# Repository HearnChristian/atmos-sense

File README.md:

# atmos-sense
Summer 2026 project to build familiarity with atmospheric sensor systems, drone integration, and all necessary concepts.

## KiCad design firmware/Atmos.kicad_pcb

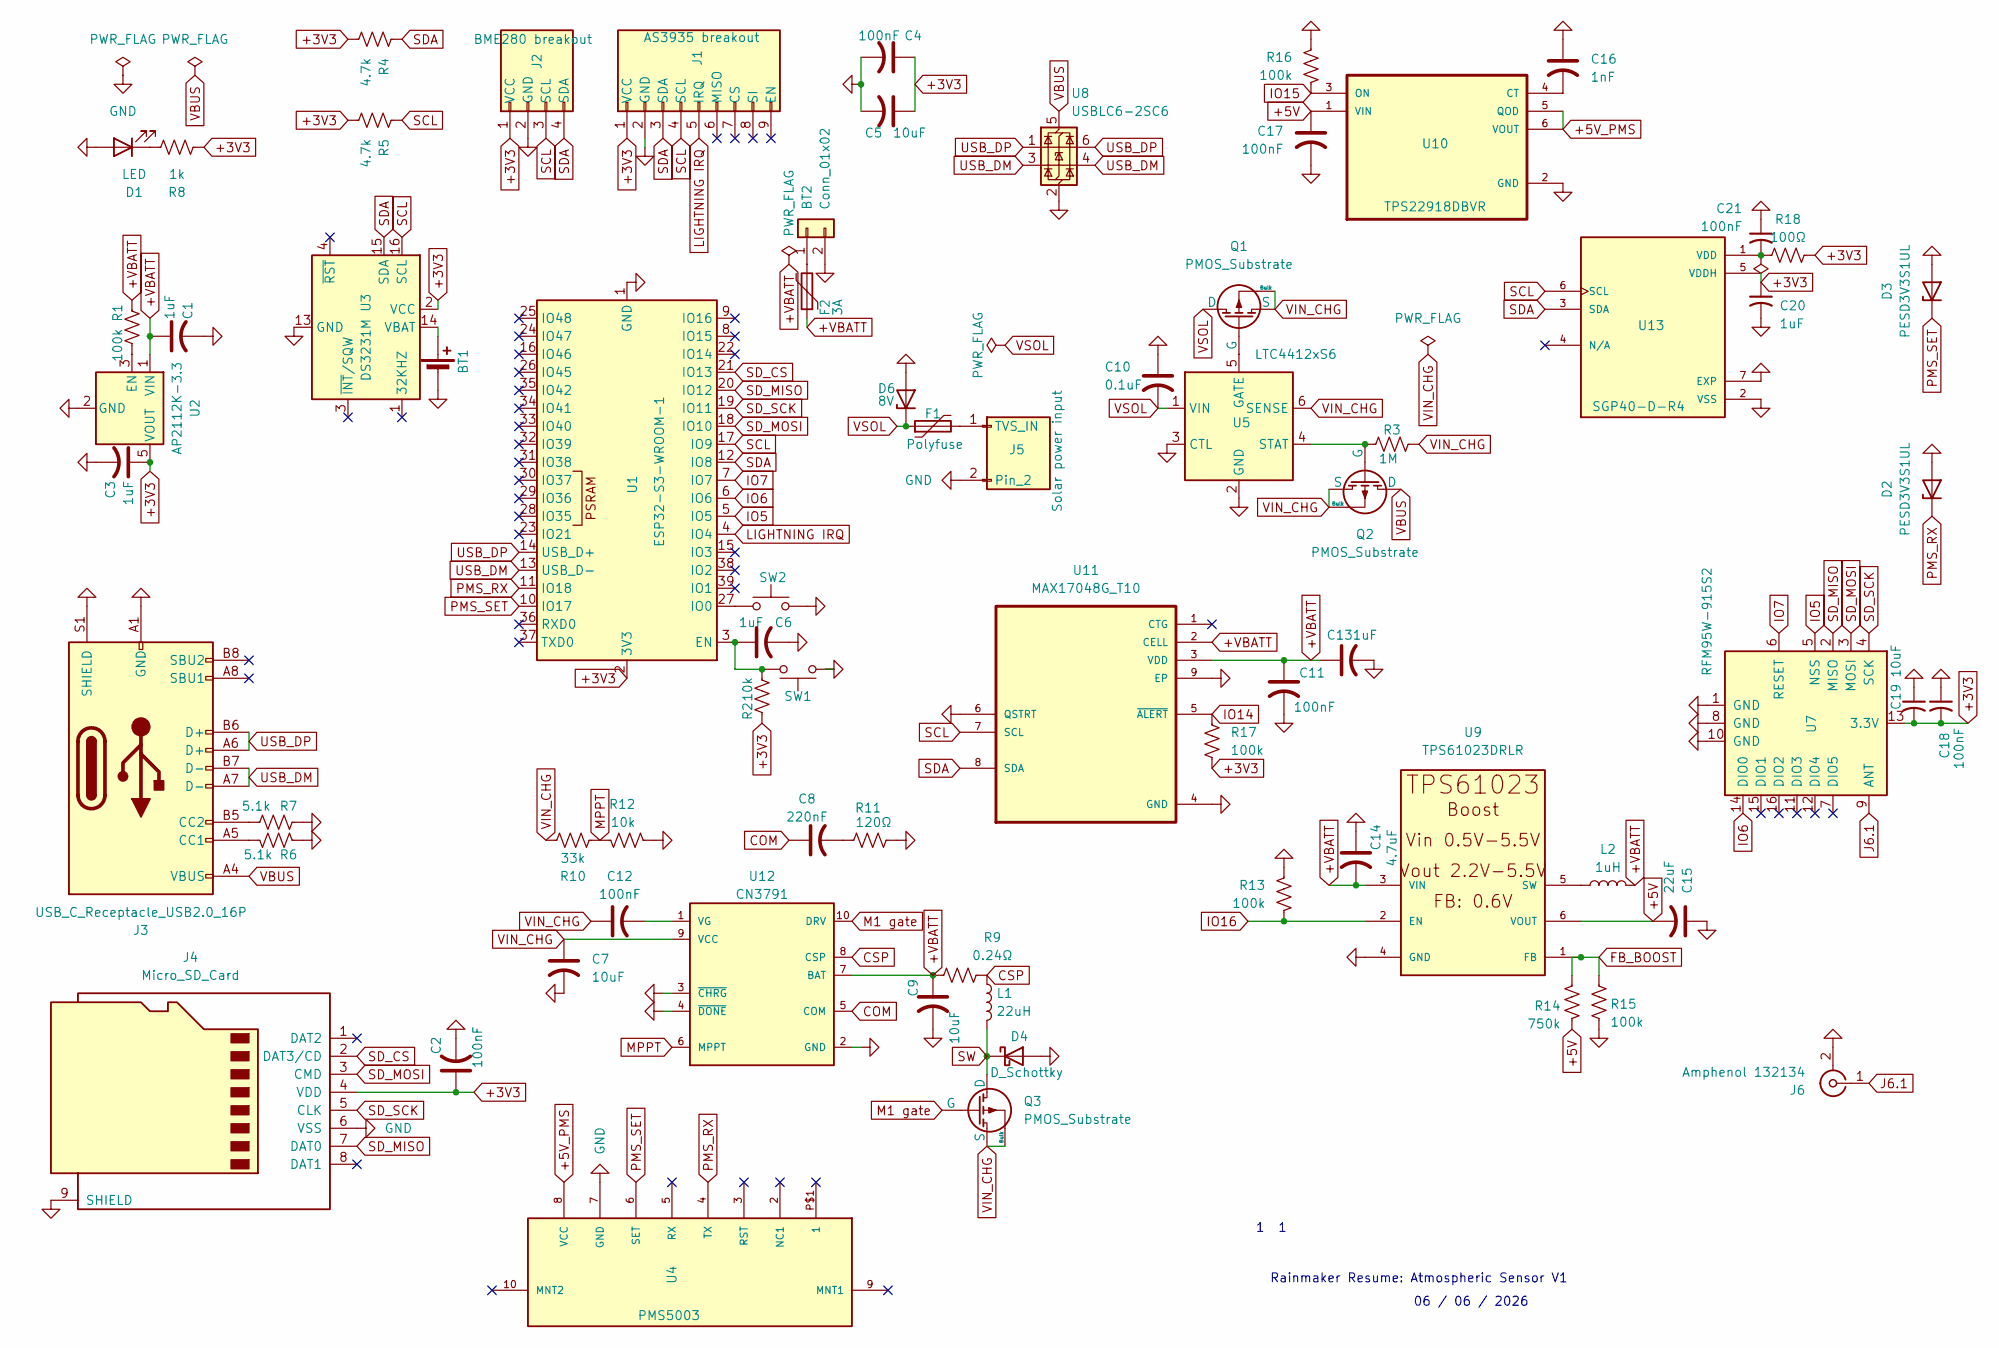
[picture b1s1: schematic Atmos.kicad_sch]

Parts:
BT1: Battery_Cell; BatteryHolder_Keystone_3034_1x20mm
BT2: Conn_01x02; JST_PH_S2B-PH-K_1x02_P2.00mm_Horizontal
C1, C3, C6, C13, C20: 1uF; C_0603_1608Metric
C2, C4, C11, C12, C17, C18, C21: 100nF; C_0603_1608Metric
C5, C7, C9, C19: 10uF; C_0805_2012Metric
C8: 220nF; C_0603_1608Metric
C10: 0.1uF; C_0603_1608Metric
C14: 4.7uF; C_0603_1608Metric
C15: 22uF; C_0805_2012Metric
C16: 1nF; C_0603_1608Metric
D1: LED; LED_0805_2012Metric
D2, D3: PESD3V3S1UL; D_SOD-882
D4: D_Schottky; D_SMA
D6: 8V; D_SOD-123
F1: Polyfuse; Fuse_1812_4532Metric
F2: 3A; Fuse_1812_4532Metric
J1: AS3935 breakout; PinSocket_1x09_P2.54mm_Vertical
J2: BME280 breakout; PinSocket_1x04_P2.54mm_Vertical
J3: USB_C_Receptacle_USB2.0_16P; USB_C_Receptacle_HRO_TYPE-C-31-M-12
J4: Micro_SD_Card; microSD_HC_Hirose_DM3AT-SF-PEJM5
J5: Solar power input; JST_XH_B2B-XH-A_1x02_P2.50mm_Vertical
J6: Amphenol 132134; SMA_Amphenol_132134_Vertical
L1: 22uH; L_Bourns_SRN6045TA
L2: 1uH; L_Coilcraft_1008HQ_2520Metric
Q1, Q2, Q3: PMOS_Substrate; SOT-23
R1, R13, R15, R16, R17: 100k; R_0603_1608Metric
R2, R12: 10k; R_0603_1608Metric
R3: 1M; R_0603_1608Metric
R4, R5: 4.7k; R_0603_1608Metric
R6, R7: 5.1k; R_0603_1608Metric
R8: 1k; R_0603_1608Metric
R9: 0.24Ω; R_1206_3216Metric
R10: 33k; R_0603_1608Metric
R11: 120Ω; R_0603_1608Metric
R14: 750k; R_0603_1608Metric
R18: 100Ω; R_0603_1608Metric
SW1: SW_Push_1P1T_NO_CK_KMR2
SW2: SW_Push; SW_Push_1P1T_NO_CK_KMR2
U1: ESP32-S3-WROOM-1
U2: AP2112K-3.3; SOT-23-5
U3: DS3231M; SOIC-16W_7.5x10.3mm_P1.27mm
U4: PMS5003; Molex_PicoBlade_53398-0871_1x08-1MP_P1.25mm_Vertical
U5: LTC4412xS6; TSOT-23-6
U7: RFM95W-915S2; HOPERF_RFM9XW_SMD
U8: USBLC6-2SC6; SOT-23-6
U9: TPS61023DRLR; SOT-563
U10: TPS22918DBVR; SOT-23-6
U11: MAX17048G_T10; DFN-8-1EP_2x2mm_P0.5mm_EP0.9x1.5mm
U12: CN3791; MSOP-10_3x3mm_P0.5mm
U13: SGP40-D-R4; DFN-6-1EP_2x2mm_P0.5mm_EP0.7x1.6mm; PARTREV 1.2

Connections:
+3V3: C2.1, C3.1, C4.1, C5.1, C18.2, C19.2, C20.1, J1.1 (VCC), J2.1 (VCC), J4.4 (VDD), R2.2, R4.2, R5.2, R8.1, R17.2, R18.2, U1.2 (3V3), U2.5 (VOUT), U3.2 (VCC), U7.13 (3.3V), U13.5 (VDDH)
+5V: C15.2, C17.1, R14.2, U9.6 (VOUT), U10.1 (VIN)
+5V_PMS: U4.8 (VCC), U10.5 (QOD), U10.6 (VOUT)
+VBATT: C1.1, C9.1, C11.1, C13.1, C14.2, F2.1, L2.2, R1.1, R9.1, U2.1 (VIN), U9.3 (VIN), U11.2 (CELL), U11.3 (VDD), U12.7 (BAT)
COM: C8.1, U12.5 (COM)
CSP: L1.1, R9.2, U12.8 (CSP)
FB_BOOST: R14.1, R15.1, U9.1 (FB)
GND: BT1.2 (-), BT2.2, C1.2, C2.2, C3.2, C4.2, C5.2, C6.2, C7.2, C9.2, C10.1, C11.2, C13.2, C14.1, C15.1, C16.1, C17.2, C18.1, C19.1, C20.2, C21.1, D1.2 (A), D2.2 (A), D3.2 (A), D4.2 (A), D6.2 (A), J1.2 (GND), J2.2 (GND), J3.A1 (GND), J3.A12 (GND), J3.B1 (GND), J3.B12 (GND), J3.S1 (SHIELD), J4.6 (VSS), J4.9 (SHIELD), J5.2, J6.2 (Ext), R6.2, R7.2, R11.2, R12.2, R13.1, R15.2, R16.1, SW1.1, SW2.2, U1.1 (GND), U1.40 (GND), U1.41 (GND), U2.2 (GND), U3.5 (GND), U3.6 (GND), U3.7 (GND), U3.8 (GND), U3.9 (GND), U3.10 (GND), U3.11 (GND), U3.12 (GND), U3.13 (GND), U4.7 (GND), U5.2 (GND), U5.3 (CTL), U7.1 (GND), U7.8 (GND), U7.10 (GND), U8.2 (GND), U9.4 (GND), U10.2 (GND), U11.4 (GND), U11.6 (QSTRT), U11.9 (EP), U12.2 (GND), U12.3 (~CHRG), U12.4 (~DONE), U13.2 (VSS), U13.7 (EXP)
IO5: U1.5 (IO5), U7.5 (NSS)
IO6: U1.6 (IO6), U7.14 (DIO0)
IO7: U1.7 (IO7), U7.6 (RESET)
IO14: R17.1, U11.5 (~ALERT)
IO15: R16.2, U10.3 (ON)
IO16: R13.2, U9.2 (EN)
J6.1: J6.1 (In), U7.9 (ANT)
LIGHTNING IRQ: J1.5 (IRQ), U1.4 (IO4)
M1 gate: Q3.2 (G), U12.10 (DRV)
MPPT: R10.1, R12.1, U12.6 (MPPT)
unnamed: BT1.1 (+), U3.14 (VBAT)
unnamed: BT2.1, F2.2
unnamed: C8.2, R11.1
unnamed: D1.1 (K), R8.2
unnamed: J3.A5 (CC1), R6.1
unnamed: J3.B5 (CC2), R7.1
unnamed: F1.2, J5.1 (TVS_IN)
unnamed: Q1.2 (G), U5.5 (GATE)
unnamed: Q2.2 (G), R3.1, U5.4 (STAT)
unnamed: C6.1, R2.1, SW1.2, U1.3 (EN)
unnamed: SW2.1, U1.27 (IO0)
unnamed: R1.2, U2.3 (EN)
unnamed: L2.1, U9.5 (SW)
unnamed: C16.2, U10.4 (CT)
unnamed: C12.2, U12.1 (VG)
unnamed: C21.2, R18.1, U13.1 (VDD)
PMS_RX: D2.1 (K), U1.11 (IO18), U4.4 (TX)
PMS_SET: D3.1 (K), U1.10 (IO17), U4.6 (SET)
SCL: J1.4 (SCL), J2.3 (SCL), R5.1, U1.17 (IO9), U3.16 (SCL), U11.7 (SCL), U13.6 (SCL)
SDA: J1.3 (SDA), J2.4 (SDA), R4.1, U1.12 (IO8), U3.15 (SDA), U11.8 (SDA), U13.3 (SDA)
SD_CS: J4.2 (DAT3/CD), U1.21 (IO13)
SD_MISO: J4.7 (DAT0), U1.20 (IO12), U7.2 (MISO)
SD_MOSI: J4.3 (CMD), U1.18 (IO10), U7.3 (MOSI)
SD_SCK: J4.5 (CLK), U1.19 (IO11), U7.4 (SCK)
SW: D4.1 (K), L1.2, Q3.1 (D)
USB_DM: J3.A7 (D-), J3.B7 (D-), U1.13 (USB_D-), U8.3 (I/O2), U8.4 (I/O2)
USB_DP: J3.A6 (D+), J3.B6 (D+), U1.14 (USB_D+), U8.1 (I/O1), U8.6 (I/O1)
VBUS: J3.A4 (VBUS), J3.A9 (VBUS), J3.B4 (VBUS), J3.B9 (VBUS), Q2.1 (D), U8.5 (VBUS)
VIN_CHG: C7.1, C12.1, Q1.3 (S), Q1.4 (Bulk), Q2.3 (S), Q2.4 (Bulk), Q3.3 (S), Q3.4 (Bulk), R3.2, R10.2, U5.6 (SENSE), U12.9 (VCC)
VSOL: C10.2, D6.1 (K), F1.1, Q1.1 (D), U5.1 (VIN)

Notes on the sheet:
06 / 06 / 2026
1 1
Rainmaker Resume: Atmospheric Sensor V1

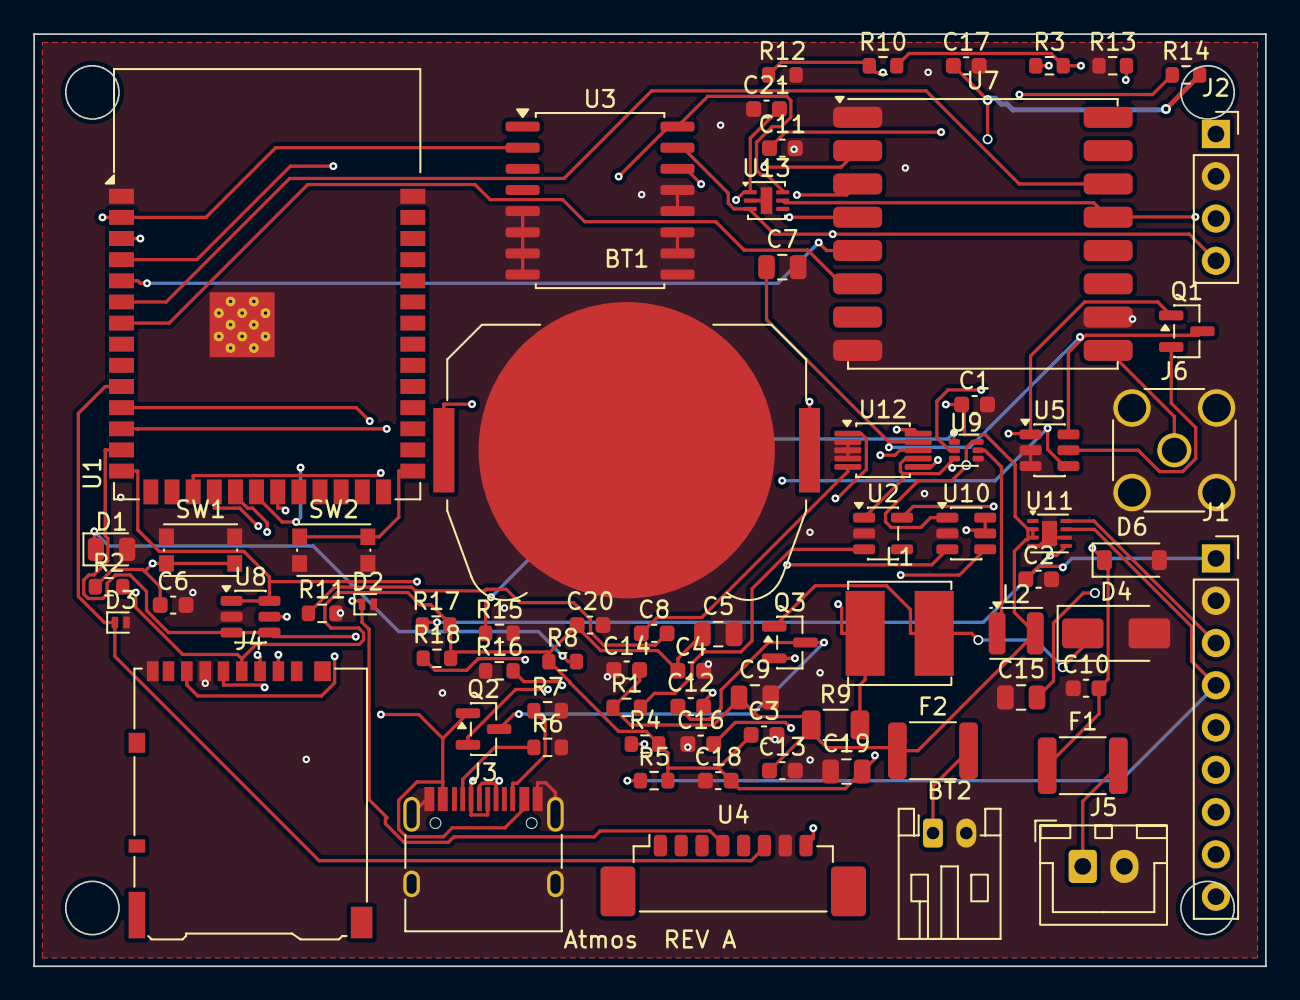
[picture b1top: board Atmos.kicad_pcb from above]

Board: 4 copper layers, 74.0 x 56.0 mm, 73 parts (0 on the bottom side), 48 nets.

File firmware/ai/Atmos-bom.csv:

"Refs","Value","Footprint","Qty","DNP"
"BT1","Battery_Cell","Battery:BatteryHolder_Keystone_3034_1x20mm","1",""
"BT2","Conn_01x02","Connector_JST:JST_PH_S2B-PH-K_1x02_P2.00mm_Horizontal","1",""
"C1","1uF","Capacitor_SMD:C_0603_1608Metric","1",""
"C2","100nF","Capacitor_SMD:C_0603_1608Metric","1",""
"C3","1uF","Capacitor_SMD:C_0603_1608Metric","1",""
"C4","100nF","Capacitor_SMD:C_0603_1608Metric","1",""
"C5","10uF","Capacitor_SMD:C_0805_2012Metric","1",""
"C6","1uF","Capacitor_SMD:C_0603_1608Metric","1",""
"C7","10uF","Capacitor_SMD:C_0805_2012Metric","1",""
"C8","220nF","Capacitor_SMD:C_0603_1608Metric","1",""
"C9","10uF","Capacitor_SMD:C_0805_2012Metric","1",""
"C10","0.1uF","Capacitor_SMD:C_0603_1608Metric","1",""
"C11","100nF","Capacitor_SMD:C_0603_1608Metric","1",""
"C12","100nF","Capacitor_SMD:C_0603_1608Metric","1",""
"C13","1uF","Capacitor_SMD:C_0603_1608Metric","1",""
"C14","4.7uF","Capacitor_SMD:C_0603_1608Metric","1",""
"C15","22uF","Capacitor_SMD:C_0805_2012Metric","1",""
"C16","1nF","Capacitor_SMD:C_0603_1608Metric","1",""
"C17","100nF","Capacitor_SMD:C_0603_1608Metric","1",""
"C18","100nF","Capacitor_SMD:C_0603_1608Metric","1",""
"C19","10uF","Capacitor_SMD:C_0805_2012Metric","1",""
"C20","1uF","Capacitor_SMD:C_0603_1608Metric","1",""
"C21","100nF","Capacitor_SMD:C_0603_1608Metric","1",""
"D1","LED","LED_SMD:LED_0805_2012Metric","1",""
"D2","PESD3V3S1UL","Diode_SMD:D_SOD-882","1",""
"D3","PESD3V3S1UL","Diode_SMD:D_SOD-882","1",""
"D4","D_Schottky","Diode_SMD:D_SMA","1",""
"D6","8V","Diode_SMD:D_SOD-123","1",""
"F1","Polyfuse","Fuse:Fuse_1812_4532Metric","1",""
"F2","3A","Fuse:Fuse_1812_4532Metric","1",""
"J1","AS3935 breakout","Connector_PinSocket_2.54mm:PinSocket_1x09_P2.54mm_Vertical","1",""
"J2","BME280 breakout","Connector_PinSocket_2.54mm:PinSocket_1x04_P2.54mm_Vertical","1",""
"J3","USB_C_Receptacle_USB2.0_16P","Connector_USB:USB_C_Receptacle_HRO_TYPE-C-31-M-12","1",""
"J4","Micro_SD_Card","Connector_Card:microSD_HC_Hirose_DM3AT-SF-PEJM5","1",""
"J5","Solar power input","Connector_JST:JST_XH_B2B-XH-A_1x02_P2.50mm_Vertical","1",""
"J6","Amphenol 132134","Connector_Coaxial:SMA_Amphenol_132134_Vertical","1",""
"L1","22uH","Inductor_SMD:L_Bourns_SRN6045TA","1",""
"L2","1uH","Inductor_SMD:L_Coilcraft_1008HQ_2520Metric","1",""
"Q1","PMOS_Substrate","Package_TO_SOT_SMD:SOT-23","1",""
"Q2","PMOS_Substrate","Package_TO_SOT_SMD:SOT-23","1",""
"Q3","PMOS_Substrate","Package_TO_SOT_SMD:SOT-23","1",""
"R1","100k","Resistor_SMD:R_0603_1608Metric","1",""
"R2","10k","Resistor_SMD:R_0603_1608Metric","1",""
"R3","1M","Resistor_SMD:R_0603_1608Metric","1",""
"R4","4.7k","Resistor_SMD:R_0603_1608Metric","1",""
"R5","4.7k","Resistor_SMD:R_0603_1608Metric","1",""
"R6","5.1k","Resistor_SMD:R_0603_1608Metric","1",""
"R7","5.1k","Resistor_SMD:R_0603_1608Metric","1",""
"R8","1k","Resistor_SMD:R_0603_1608Metric","1",""
"R9","0.24Ω","Resistor_SMD:R_1206_3216Metric","1",""
"R10","33k","Resistor_SMD:R_0603_1608Metric","1",""
"R11","120Ω","Resistor_SMD:R_0603_1608Metric","1",""
"R12","10k","Resistor_SMD:R_0603_1608Metric","1",""
"R13","100k","Resistor_SMD:R_0603_1608Metric","1",""
"R14","750k","Resistor_SMD:R_0603_1608Metric","1",""
"R15","100k","Resistor_SMD:R_0603_1608Metric","1",""
"R16","100k","Resistor_SMD:R_0603_1608Metric","1",""
"R17","100k","Resistor_SMD:R_0603_1608Metric","1",""
"R18","100Ω","Resistor_SMD:R_0603_1608Metric","1",""
"SW1","~","Button_Switch_SMD:SW_Push_1P1T_NO_CK_KMR2","1",""
"SW2","SW_Push","Button_Switch_SMD:SW_Push_1P1T_NO_CK_KMR2","1",""
"U1","ESP32-S3-WROOM-1","RF_Module:ESP32-S3-WROOM-1","1",""
"U2","AP2112K-3.3","Package_TO_SOT_SMD:SOT-23-5","1",""
"U3","DS3231M","Package_SO:SOIC-16W_7.5x10.3mm_P1.27mm","1",""
"U4","PMS5003","Connector_Molex:Molex_PicoBlade_53398-0871_1x08-1MP_P1.25mm_Vertical","1",""
"U5","LTC4412xS6","Package_TO_SOT_SMD:TSOT-23-6","1",""
"U7","RFM95W-915S2","RF_Module:HOPERF_RFM9XW_SMD","1",""
"U8","USBLC6-2SC6","Package_TO_SOT_SMD:SOT-23-6","1",""
"U9","TPS61023DRLR","Package_TO_SOT_SMD:SOT-563","1",""
"U10","TPS22918DBVR","Package_TO_SOT_SMD:SOT-23-6","1",""
"U11","MAX17048G_T10","Package_DFN_QFN:DFN-8-1EP_2x2mm_P0.5mm_EP0.9x1.5mm","1",""
"U12","CN3791","Package_SO:MSOP-10_3x3mm_P0.5mm","1",""
"U13","SGP40-D-R4","Package_DFN_QFN:DFN-6-1EP_2x2mm_P0.5mm_EP0.7x1.6mm","1",""

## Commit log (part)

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2026-06-02 Add files via upload
    V1 schematic
2026-06-06 Add files via upload
    Expanded version of V1
2026-06-06 Sync latest schematic + add AI exports (PDF/netlist/BOM) for browser-Claude
2026-06-06 U5 LTC4412xS6 wired
2026-06-06 fixed U12 wiring
2026-06-07 wired J5 solar
2026-06-07 sanity
2026-06-07 BT2 wired
2026-06-07 U11 wired
2026-06-07 U11 touchup
2026-06-07 TPS init
2026-06-07 TPS progress
2026-06-07 TPS finished
2026-06-07 RF component + Antenna
2026-06-07 USBLC6 done
2026-06-07 added diodes
2026-06-07 Schematic tentatively finished
2026-06-07 Schematic fully finished -hierarchies
2026-06-10 updated a few values
